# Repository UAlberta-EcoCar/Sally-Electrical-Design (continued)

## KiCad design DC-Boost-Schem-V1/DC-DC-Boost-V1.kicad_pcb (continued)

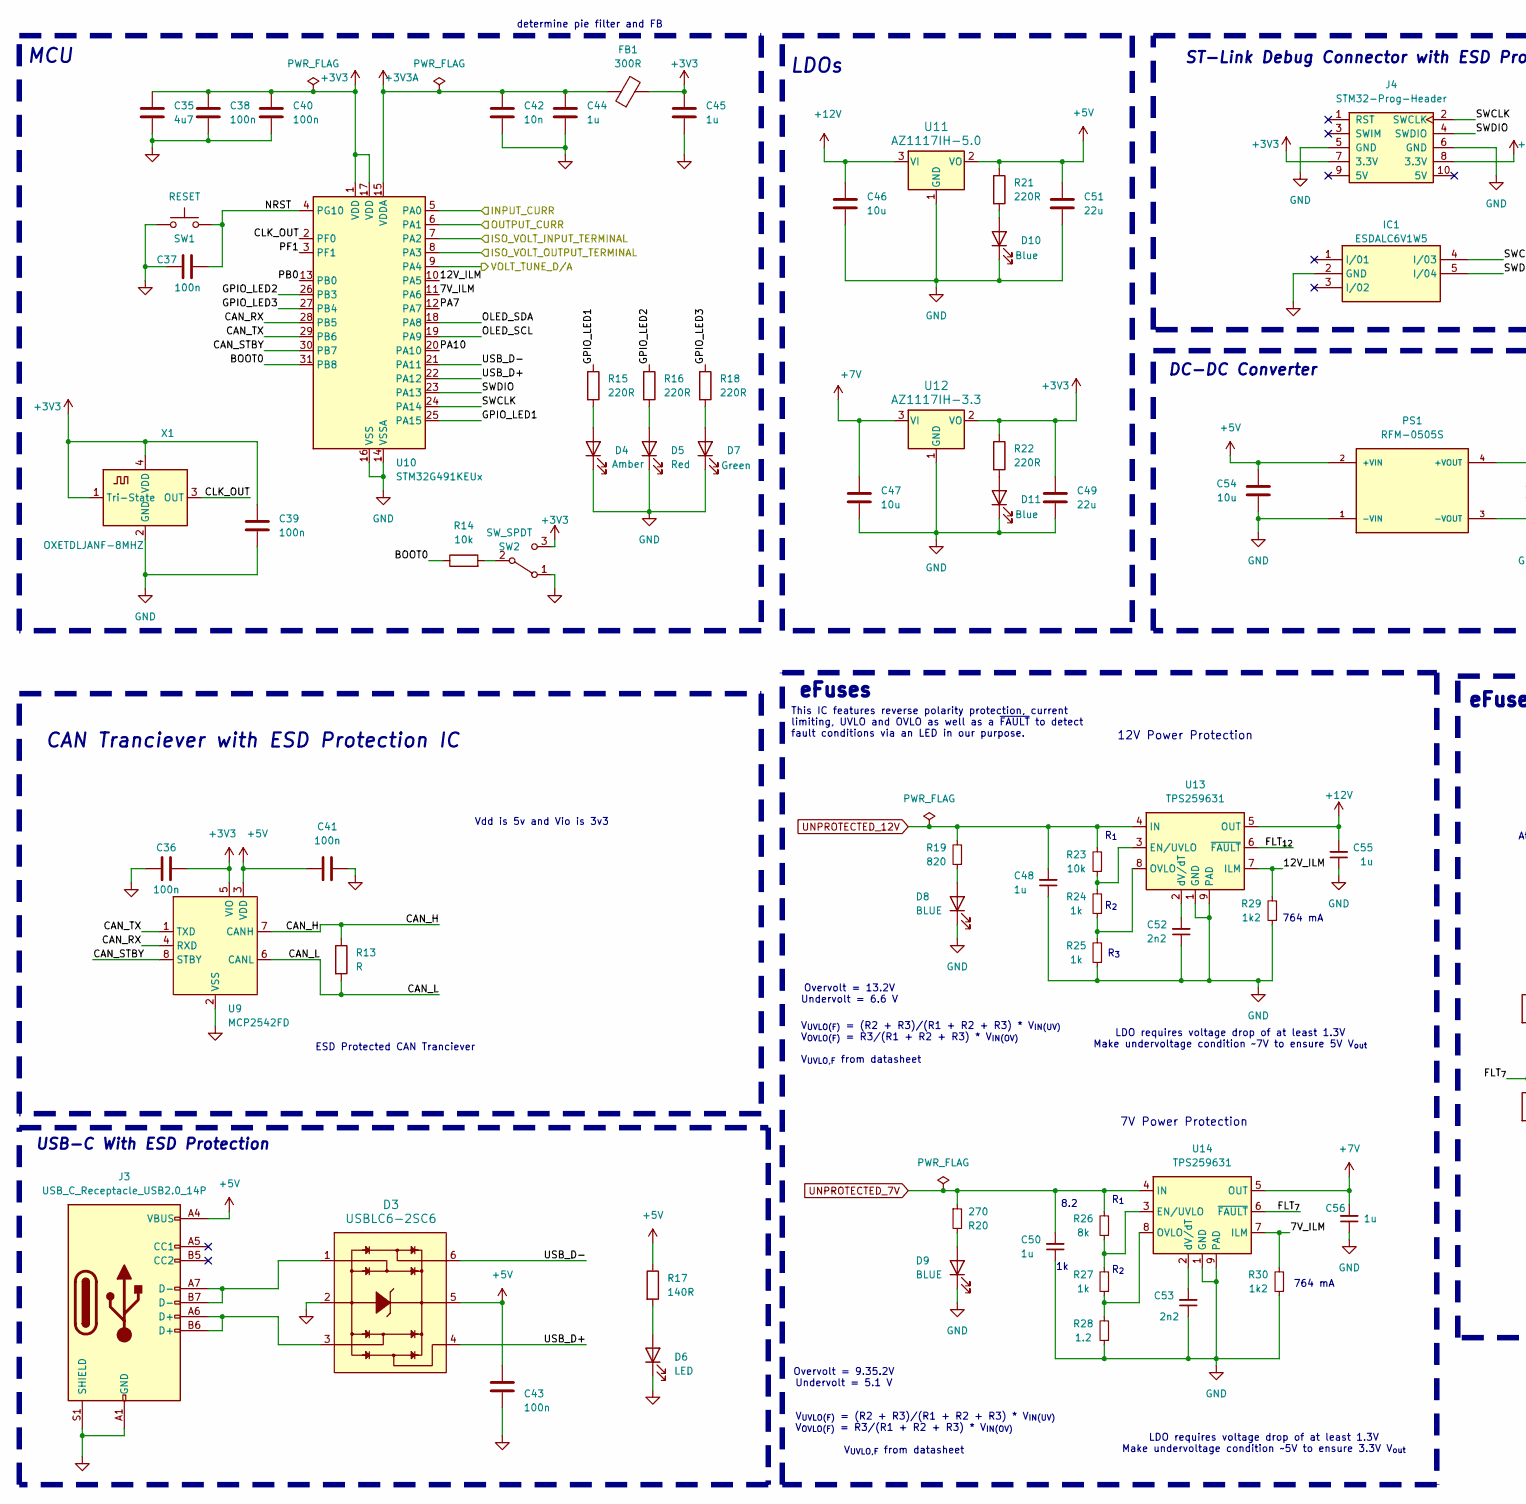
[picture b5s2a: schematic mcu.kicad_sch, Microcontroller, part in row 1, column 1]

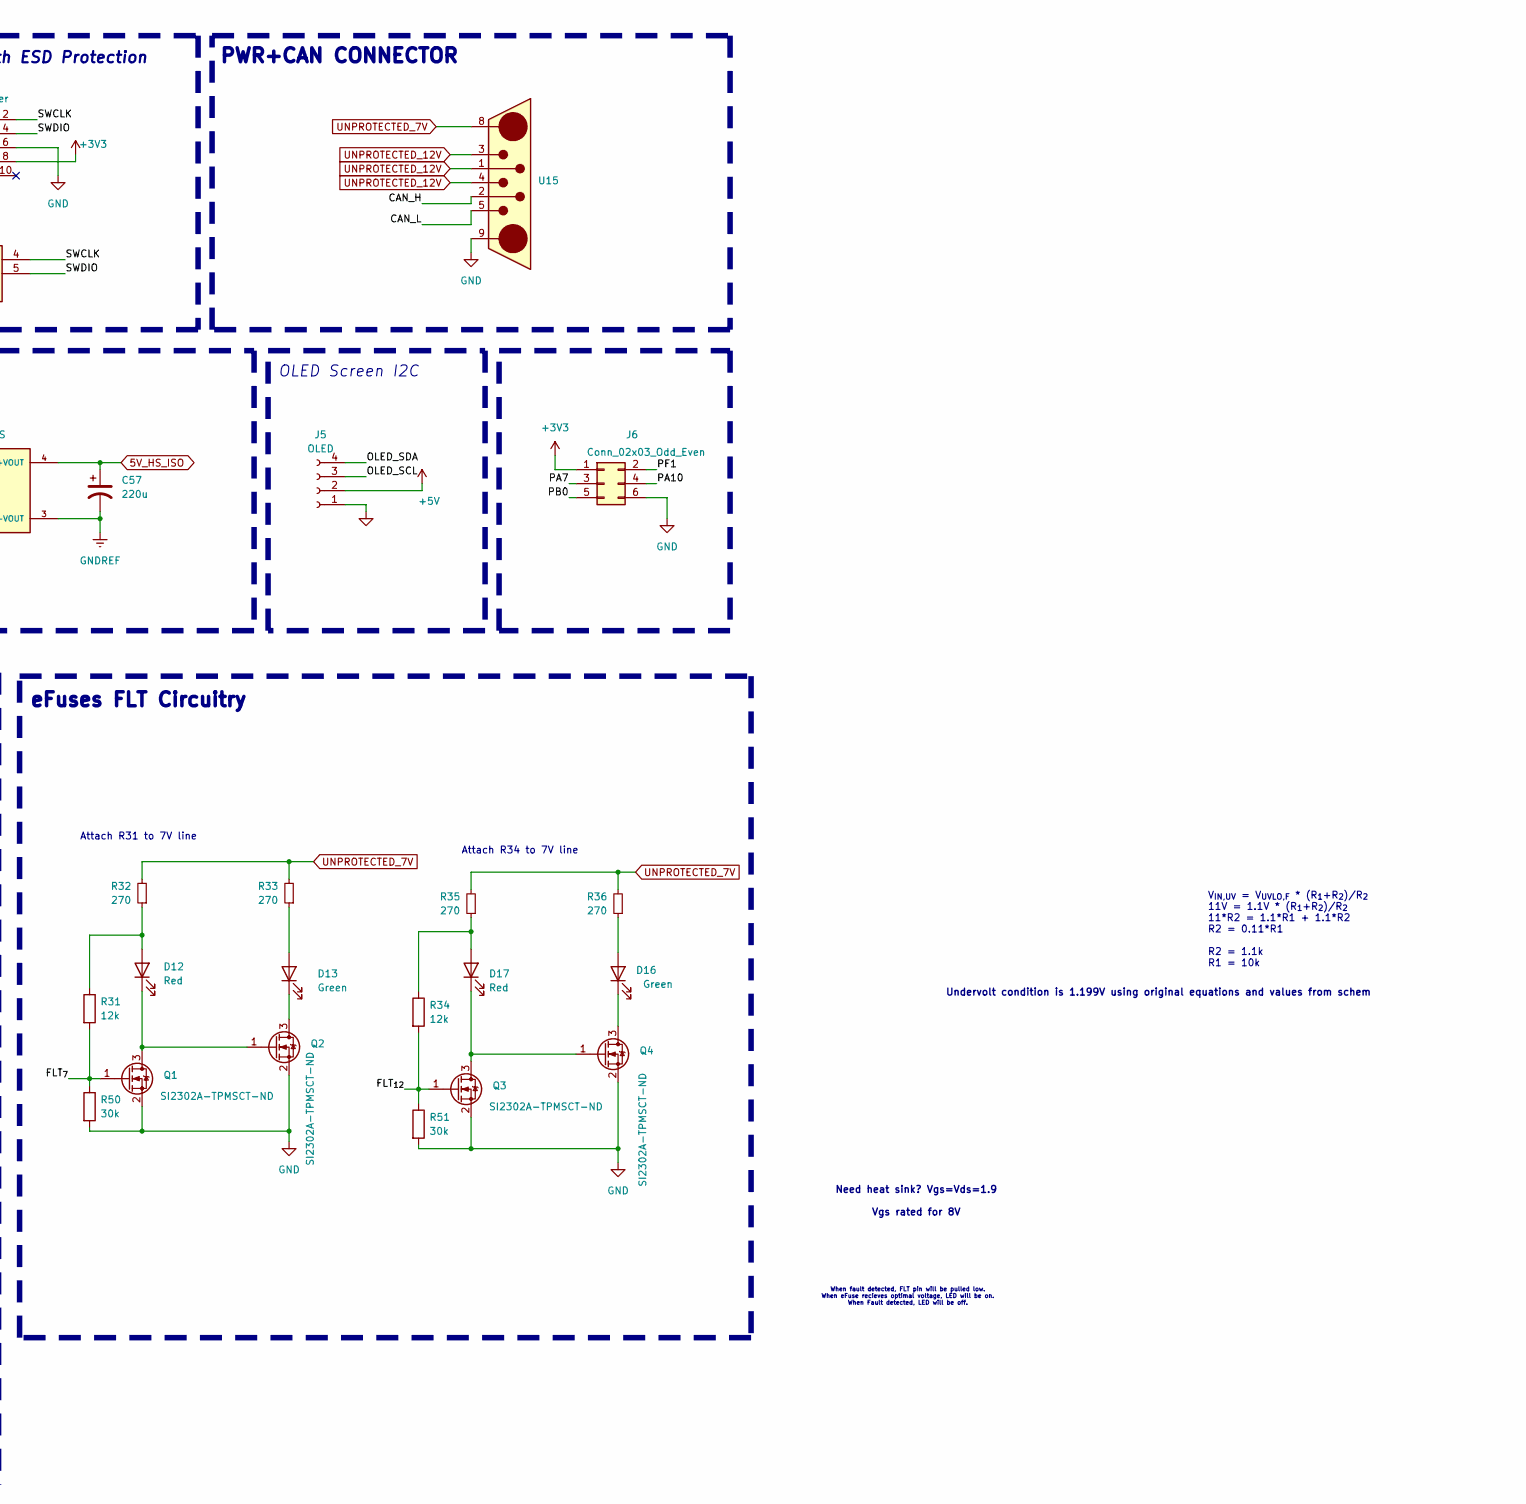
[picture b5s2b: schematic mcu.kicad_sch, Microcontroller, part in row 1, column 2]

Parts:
C35: 4u7; C_0603_1608Metric; JLCPCB Part#(Optional) C96446
C36, C37, C38, C40, C41, C43: 100n; C_0603_1608Metric; JLCPCB Part#(Optional) C1525
C39: 100n; C_0603_1608Metric
C42: 10n; C_0603_1608Metric; JLCPCB Part#(Optional) C96446
C44, C45: 1u; C_0603_1608Metric; JLCPCB Part#(Optional) C28323
C46, C47, C54: 10u; C_0603_1608Metric
C48, C50, C55, C56: 1u; C_0603_1608Metric; Part# C15849
C49, C51: 22u; C_0603_1608Metric
C52, C53: 2n2; C_0603_1608Metric; Part# C1604
C57: 220u; CP_Elec_6.3x5.8
D3: USBLC6-2SC6; SOT95P280X145-6N; Digikey # 497-5235-1-ND
D4: Amber; LED_0805_2012Metric
D5: Red; LED_0805_2012Metric
D6: LED; LED_0603_1608Metric
D7: Green; LED_0805_2012Metric
D8, D9: BLUE; LED_0603_1608Metric; Part# C72041
D10, D11: Blue; LED_0603_1608Metric
D12, D17: Red; LED_0603_1608Metric; Part# C72043
D13, D16: Green; LED_0603_1608Metric; Part# C72043
FB1: 300R; L_0603_1608Metric; Digikey # 1934-1474-1-ND
IC1: ESDALC6V1W5; SOT65P210X110-5N; JLCPCB Part#(Optional) C2827626
J3: USB_C_Receptacle_USB2.0_14P; USB_C_Receptacle_GCT_USB4105-xx-A_16P_TopMnt_Horizontal
J4: STM32-Prog-Header; IDC-STM32-Prog-Header_2x05_P2.54mm_Vertical
J5: OLED; Display_128x64_096_I2C
J6: Conn_02x03_Odd_Even; PinHeader_2x03_P2.54mm_Vertical
PS1: RFM-0505S; CONV_RFM-0505S; PARTREV 0
Q1, Q2, Q3, Q4: SI2302A-TPMSCT-ND; SOT-23-3_Adjusted; Part# SI2302A-TPMSCT-ND
R13: R; R_0603_1608Metric
R14, R23: 10k; R_0603_1608Metric
R15, R16, R18: 220R; R_0805_2012Metric
R17: 140R; R_0603_1608Metric
R19: 820; R_0603_1608Metric; Part# C23253
R20, R32, R33, R35, R36: 270; R_0603_1608Metric; Part# C22966
R21, R22: 220R; R_0603_1608Metric
R24, R25, R27: 1k; R_0603_1608Metric
R26: 8k; R_0603_1608Metric
R28: 1.2; R_0603_1608Metric
R29, R30: 1k2; R_0603_1608Metric
R31, R34: 12k; R_0603_1608Metric
R50, R51: 30k; R_0603_1608Metric
SW1: RESET; SW_PUSH_6mm_H5mm; Part # C2689510
SW2: SW_SPDT; SW_SPDT_PCM12; Digikey # 2223-SLW-66527511-SMT-TRCT-ND
U9: MCP2542FD; SOIC-8_3.9x4.9mm_P1.27mm
U10: STM32G491KEUx; QFN-32-1EP_5x5mm_P0.5mm_EP3.45x3.45mm
U11: AZ1117IH-5.0; SOT-223-3_TabPin2
U12: AZ1117IH-3.3; SOT-223-3_TabPin2
U13, U14: TPS259631; TI_SO-PowerPAD-8
U15: DB7W2-Male
X1: OXETDLJANF-8MHZ; Crystal_SMD_3225-4Pin_3.2x2.5mm

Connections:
5V_HS_ISO: C57.1, PS1.4 (+VOUT); also elsewhere on the board
+3V3: C35.1, C36.2, C38.1, C39.1, C40.1, C45.1, C49.1, FB1.2, J4.7 (3.3V), J4.8 (3.3V), J6.1, R22.1, SW2.3 (C), U9.5 (VIO), U10.1 (VDD), U10.17 (VDD), U12.2 (VO), X1.1 (Tri-State), X1.4 (VDD)
+3V3A: C42.1, C44.1, FB1.1, U10.15 (VDDA)
+5V: C41.2, C43.2, C51.1, C54.1, D3.5, J3.A4 (VBUS), J3.A9 (VBUS), J3.B4 (VBUS), J3.B9 (VBUS), J5.2, PS1.2 (+VIN), R17.1, R21.1, U9.3 (VDD), U11.2 (VO); also elsewhere on the board
+7V: C47.1, C56.2, U12.3 (VI), U14.5 (OUT)
+12V: C46.1, C55.2, U11.3 (VI), U13.5 (OUT)
/Boost-Circuit/INPUT_CURR: U10.5 (PA0); also elsewhere on the board
/Boost-Circuit/OUTPUT_CURR: U10.6 (PA1); also elsewhere on the board
/MCU+POWER+CAN/7V_ILM: R30.2, U10.11 (PA6), U14.7 (ILM)
/MCU+POWER+CAN/12V_ILM: R29.2, U10.10 (PA5), U13.7 (ILM)
/MCU+POWER+CAN/BOOT0: R14.1, U10.31 (PB8)
/MCU+POWER+CAN/CAN_H: R13.1, U9.7 (CANH), U15.2
/MCU+POWER+CAN/CAN_L: R13.2, U9.6 (CANL), U15.5
/MCU+POWER+CAN/CAN_RX: U9.4 (RXD), U10.28 (PB5)
/MCU+POWER+CAN/CAN_STBY: U9.8 (STBY), U10.30 (PB7)
/MCU+POWER+CAN/CAN_TX: U9.1 (TXD), U10.29 (PB6)
/MCU+POWER+CAN/CLK_OUT: U10.2 (PF0), X1.3 (OUT)
/MCU+POWER+CAN/FLT_{7}: Q1.1 (G), R31.2, R50.1, U14.6 (~FAULT)
/MCU+POWER+CAN/FLT_{12}: Q3.1 (G), R34.2, R51.1, U13.6 (~FAULT)
/MCU+POWER+CAN/GPIO_LED1: R15.1, U10.25 (PA15)
/MCU+POWER+CAN/GPIO_LED2: R16.1, U10.26 (PB3)
/MCU+POWER+CAN/GPIO_LED3: R18.1, U10.27 (PB4)
/MCU+POWER+CAN/ISO_VOLT_INPUT_TERMINAL: U10.7 (PA2); also elsewhere on the board
/MCU+POWER+CAN/ISO_VOLT_OUTPUT_TERMINAL: U10.8 (PA3); also elsewhere on the board
/MCU+POWER+CAN/NRST: C37.2, SW1.2, U10.4 (PG10)
/MCU+POWER+CAN/OLED_SCL: J5.3, U10.19 (PA9)
/MCU+POWER+CAN/OLED_SDA: J5.4, U10.18 (PA8)
/MCU+POWER+CAN/PA7: J6.3, U10.12 (PA7)
/MCU+POWER+CAN/PA10: J6.4, U10.20 (PA10)
/MCU+POWER+CAN/PB0: J6.5, U10.13 (PB0)
/MCU+POWER+CAN/PF1: J6.2, U10.3 (PF1)
/MCU+POWER+CAN/SWCLK: IC1.4 (I/03), J4.2 (SWCLK), U10.24 (PA14)
/MCU+POWER+CAN/SWDIO: IC1.5 (I/04), J4.4 (SWDIO), U10.23 (PA13)
/MCU+POWER+CAN/USB_D+: D3.4, U10.22 (PA12)
/MCU+POWER+CAN/USB_D-: D3.6, U10.21 (PA11)
/MCU+POWER+CAN/VOLT_TUNE_D/A: U10.9 (PA4); also elsewhere on the board
GND: C35.2, C36.1, C37.1, C38.2, C39.2, C40.2, C41.1, C42.2, C43.1, C44.2, C45.2, C46.2, C47.2, C48.1, C49.2, C50.1, C51.2, C52.1, C53.1, C54.2, C55.1, C56.1, D3.2, D4.1 (K), D5.1 (K), D6.1 (K), D7.1 (K), D8.1 (K), D9.1 (K), D10.1 (K), D11.1 (K), IC1.2 (GND), J3.A1 (GND), J3.A12 (GND), J3.B1 (GND), J3.B12 (GND), J3.S1 (SHIELD), J4.5 (GND), J4.6 (GND), J5.1, J6.6, PS1.1 (-VIN), Q1.2 (S), Q2.2 (S), Q3.2 (S), Q4.2 (S), R25.1, R28.1, R29.1, R30.1, R50.2, R51.2, SW1.1, SW2.1 (A), U9.2 (VSS), U10.14 (VSSA), U10.16 (VSS), U10.32 (VSS), U10.33 (VSS), U11.1 (GND), U12.1 (GND), U13.1 (GND), U13.9 (PAD), U14.1 (GND), U14.9 (PAD), U15.9, X1.2 (GND); also elsewhere on the board
GNDREF: C57.2, PS1.3 (-VOUT); also elsewhere on the board
unnamed: D3.1, J3.A7 (D-), J3.B7 (D-)
unnamed: D3.3, J3.A6 (D+), J3.B6 (D+)
unnamed: D4.2 (A), R15.2
unnamed: D5.2 (A), R16.2
unnamed: D6.2 (A), R17.2
unnamed: D7.2 (A), R18.2
unnamed: D8.2 (A), R19.1
unnamed: D9.2 (A), R20.2
unnamed: D10.2 (A), R21.2
unnamed: D11.2 (A), R22.2
unnamed: D12.2 (A), R31.1, R32.1
unnamed: D12.1 (K), Q1.3 (D), Q2.1 (G)
unnamed: D13.2 (A), R33.1
unnamed: D13.1 (K), Q2.3 (D)
unnamed 69: D17.2 (A), R34.1, R35.1; also elsewhere on the board
unnamed 70: D17.1 (K), Q3.3 (D), Q4.1 (G); also elsewhere on the board
unnamed 71: D16.2 (A), R36.1; also elsewhere on the board
unnamed 72: D16.1 (K), Q4.3 (D); also elsewhere on the board
unnamed: R14.2, SW2.2 (B)
unnamed: R23.1, R24.2, U13.3 (EN/UVLO)
unnamed: R24.1, R25.2, U13.8 (OVLO)
unnamed: C52.2, U13.2 (dV/dT)
unnamed: R26.1, R27.2, U14.3 (EN/UVLO)
unnamed: R27.1, R28.2, U14.8 (OVLO)
unnamed: C53.2, U14.2 (dV/dT)
UNPROTECTED_7V: C50.2, R20.1, R26.2, R32.2, R33.2, R35.2, R36.2, U14.4 (IN), U15.8
UNPROTECTED_12V: C48.2, R19.2, R23.2, U13.4 (IN), U15.1, U15.3, U15.4

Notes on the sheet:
764 mA
V_{UVLO(F)} = (R2 + R3)/(R1 + R2 + R3) * V_{IN(UV)} V_{OVLO(F)} = R3/(R1 + R2 + R3) * V_{IN(OV)} V_{UVLO,F} from datasheet
V_{IN,UV} = V_{UVLO,F} * (R_{1}+R_{2})/R_{2} 11V = 1.1V * (R_{1}+R_{2})/R_{2} 11*R2 = 1.1*R1 + 1.1*R2 R2 = 0.11*R1 R2 = 1.1k R1 = 10k
Attach R31 to 7V line
Need heat sink? Vgs=Vds=1.9 Vgs rated for 8V
MCU
Undervolt condition is 1.199V using original equations and values from schem
DC-DC Converter
LDO requires voltage drop of at least 1.3V Make undervoltage condition ~7V to ensure 5V V_{out}
Overvolt = 13.2V Undervolt = 6.6 V
PWR+CAN CONNECTOR
ST-Link Debug Connector with ESD Protection
8.2
USB-C With ESD Protection
R_{1}
LDOs
CAN Tranciever with ESD Protection IC
R_{2}
LDO requires voltage drop of at least 1.3V Make undervoltage condition ~5V to ensure 3.3V V_{out}
When fault detected, FLT pin will be pulled low. When eFuse recieves optimal voltage, LED will be on. When Fault detected, LED will be off.
eFuses
ESD Protected CAN Tranciever
This IC features reverse polarity protection, current limiting, UVLO and OVLO as well as a ~{FAULT} to detect fault conditions via an LED in our purpose.
Attach R34 to 7V line
V_{UVLO(F)} = (R2 + R3)/(R1 + R2 + R3) * V_{IN(UV)} V_{OVLO(F)} = R3/(R1 + R2 + R3) * V_{IN(OV)} V_{UVLO,F} from datasheet
determine pie filter and FB
Overvolt = 9.35.2V Undervolt = 5.1 V
Vdd is 5v and Vio is 3v3
7V Power Protection
OLED Screen I2C
R_{3}
12V Power Protection
eFuses FLT Circuitry

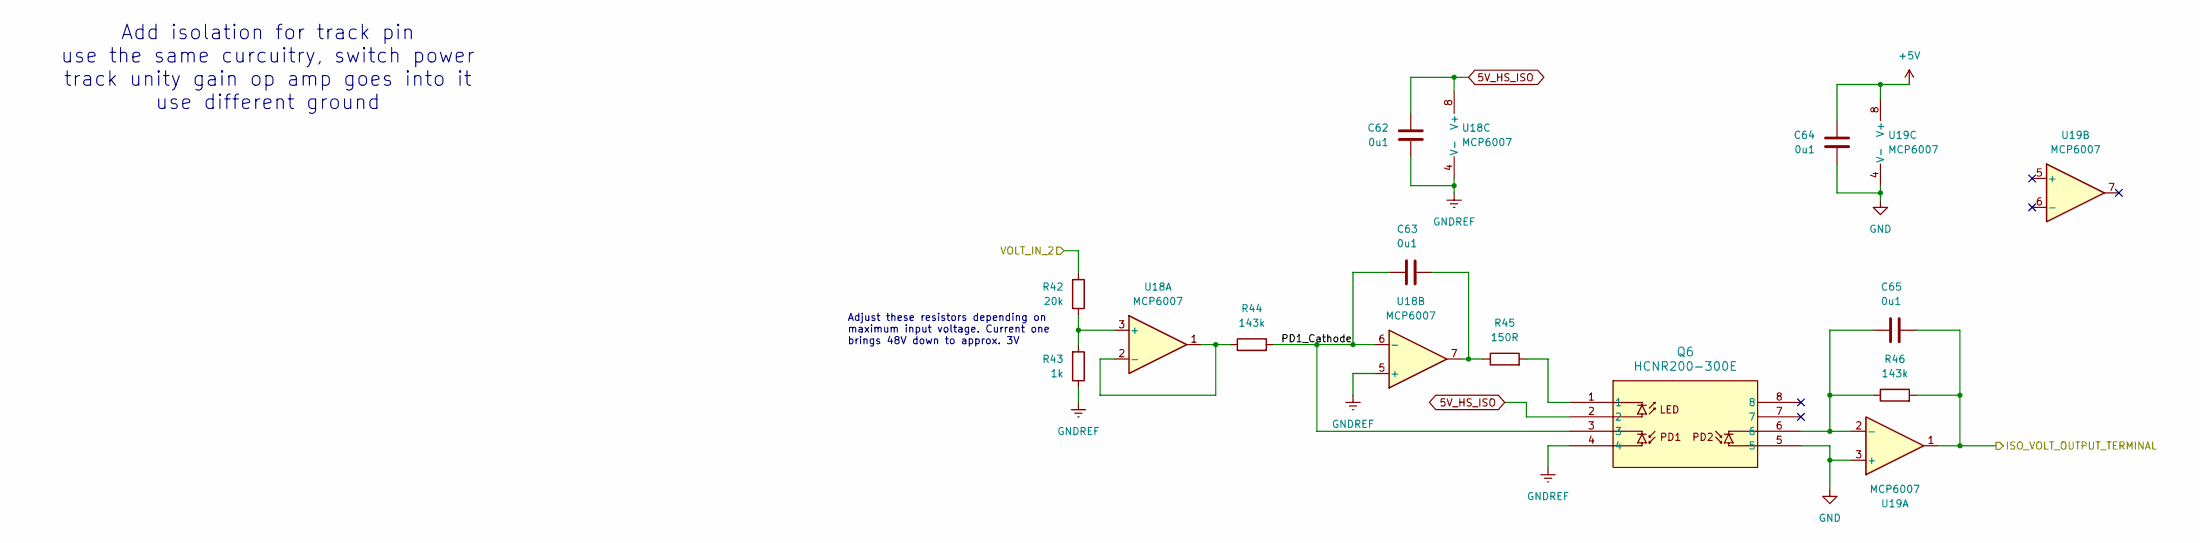
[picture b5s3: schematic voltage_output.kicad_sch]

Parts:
C62, C63, C64, C65: 0u1; C_0603_1608Metric
Q6: HCNR200-300E
R42: 20k; R_0603_1608Metric
R43: 1k; R_0603_1608Metric
R44, R46: 143k; R_0603_1608Metric
R45: 150R; R_0603_1608Metric
U18, U19: MCP6007; SOIC-8_3.9x4.9mm_P1.27mm

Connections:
5V_HS_ISO: C62.2, Q6.2, U18.8 (V+); also elsewhere on the board
+5V: C64.2, U19.8 (V+); also elsewhere on the board
/Boost-Circuit/VOLT_IN_2: R42.2; also elsewhere on the board
/MCU+POWER+CAN/ISO_VOLT_OUTPUT_TERMINAL: C65.2, R46.2, U19.1; also elsewhere on the board
/Voltage Sensing Output Terminal/PD1_Cathode: C63.1, Q6.3, R44.2, U18.6 (-)
GND: C64.1, Q6.5, U19.3 (+), U19.4 (V-); also elsewhere on the board
GNDREF: C62.1, Q6.4, R43.1, U18.4 (V-), U18.5 (+); also elsewhere on the board
unnamed: C63.2, R45.1, U18.7
unnamed: Q6.1, R45.2
unnamed: R42.1, R43.2, U18.3 (+)
unnamed: R44.1, U18.1, U18.2 (-)
unnamed: C65.1, Q6.6, R46.1, U19.2 (-)

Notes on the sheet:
Add isolation for track pin use the same curcuitry, switch power track unity gain op amp goes into it use different ground
Adjust these resistors depending on maximum input voltage. Current one brings 48V down to approx. 3V

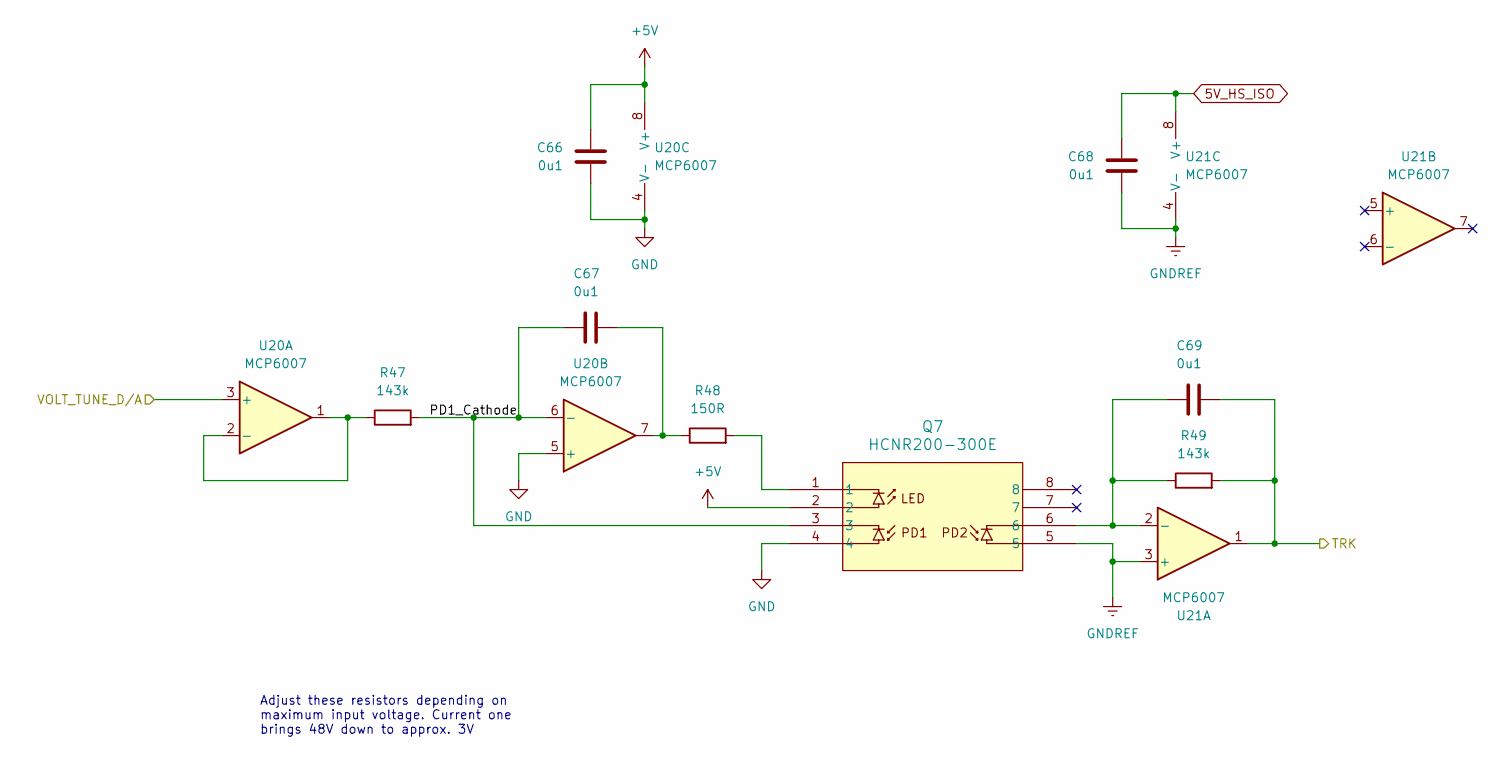
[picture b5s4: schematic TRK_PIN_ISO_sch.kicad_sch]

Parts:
C66, C67, C69: 0u1; C_0603_1608Metric
C68: 0u1; R_0603_1608Metric
Q7: HCNR200-300E
R47, R49: 143k; R_0603_1608Metric
R48: 150R; R_0603_1608Metric
U20, U21: MCP6007; SOIC-8_3.9x4.9mm_P1.27mm

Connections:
5V_HS_ISO: C68.2, U21.8 (V+); also elsewhere on the board
+5V: C66.2, Q7.2, U20.8 (V+); also elsewhere on the board
/Boost-Circuit/TRK: C69.2, R49.2, U21.1; also elsewhere on the board
/MCU+POWER+CAN/VOLT_TUNE_D/A: U20.3 (+); also elsewhere on the board
/TRK Pin Isolation/PD1_Cathode: C67.1, Q7.3, R47.2, U20.6 (-)
GND: C66.1, Q7.4, U20.4 (V-), U20.5 (+); also elsewhere on the board
GNDREF: C68.1, Q7.5, U21.3 (+), U21.4 (V-); also elsewhere on the board
unnamed: C67.2, R48.1, U20.7
unnamed: Q7.1, R48.2
unnamed: R47.1, U20.1, U20.2 (-)
unnamed: C69.1, Q7.6, R49.1, U21.2 (-)

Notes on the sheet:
Adjust these resistors depending on maximum input voltage. Current one brings 48V down to approx. 3V

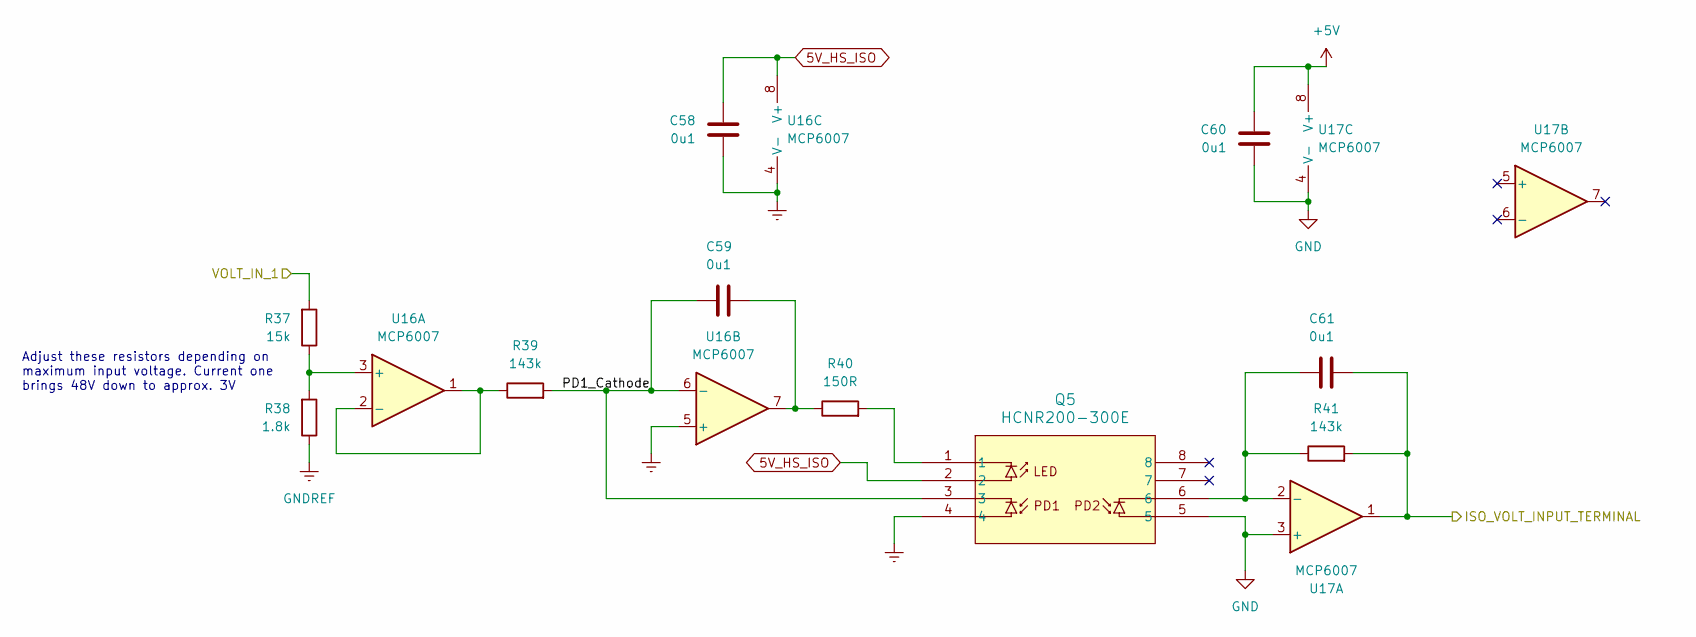
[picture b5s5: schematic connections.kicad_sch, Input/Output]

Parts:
C58, C59, C60, C61: 0u1; C_0603_1608Metric
Q5: HCNR200-300E
R37: 15k; R_0603_1608Metric
R38: 1.8k; R_0603_1608Metric
R39, R41: 143k; R_0603_1608Metric
R40: 150R; R_0603_1608Metric
U16, U17: MCP6007; SOIC-8_3.9x4.9mm_P1.27mm

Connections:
5V_HS_ISO: C58.2, Q5.2, U16.8 (V+); also elsewhere on the board
+5V: C60.2, U17.8 (V+); also elsewhere on the board
/Boost-Circuit/VOLT_IN_1: R37.2; also elsewhere on the board
/MCU+POWER+CAN/ISO_VOLT_INPUT_TERMINAL: C61.2, R41.2, U17.1; also elsewhere on the board
/Voltage Sensing Input Terminal/PD1_Cathode: C59.1, Q5.3, R39.2, U16.6 (-)
GND: C60.1, Q5.5, U17.3 (+), U17.4 (V-); also elsewhere on the board
GNDREF: C58.1, Q5.4, R38.1, U16.4 (V-), U16.5 (+); also elsewhere on the board
unnamed: C59.2, R40.1, U16.7
unnamed: Q5.1, R40.2
unnamed: R37.1, R38.2, U16.3 (+)
unnamed: R39.1, U16.1, U16.2 (-)
unnamed: C61.1, Q5.6, R41.1, U17.2 (-)

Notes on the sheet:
Adjust these resistors depending on maximum input voltage. Current one brings 48V down to approx. 3V
